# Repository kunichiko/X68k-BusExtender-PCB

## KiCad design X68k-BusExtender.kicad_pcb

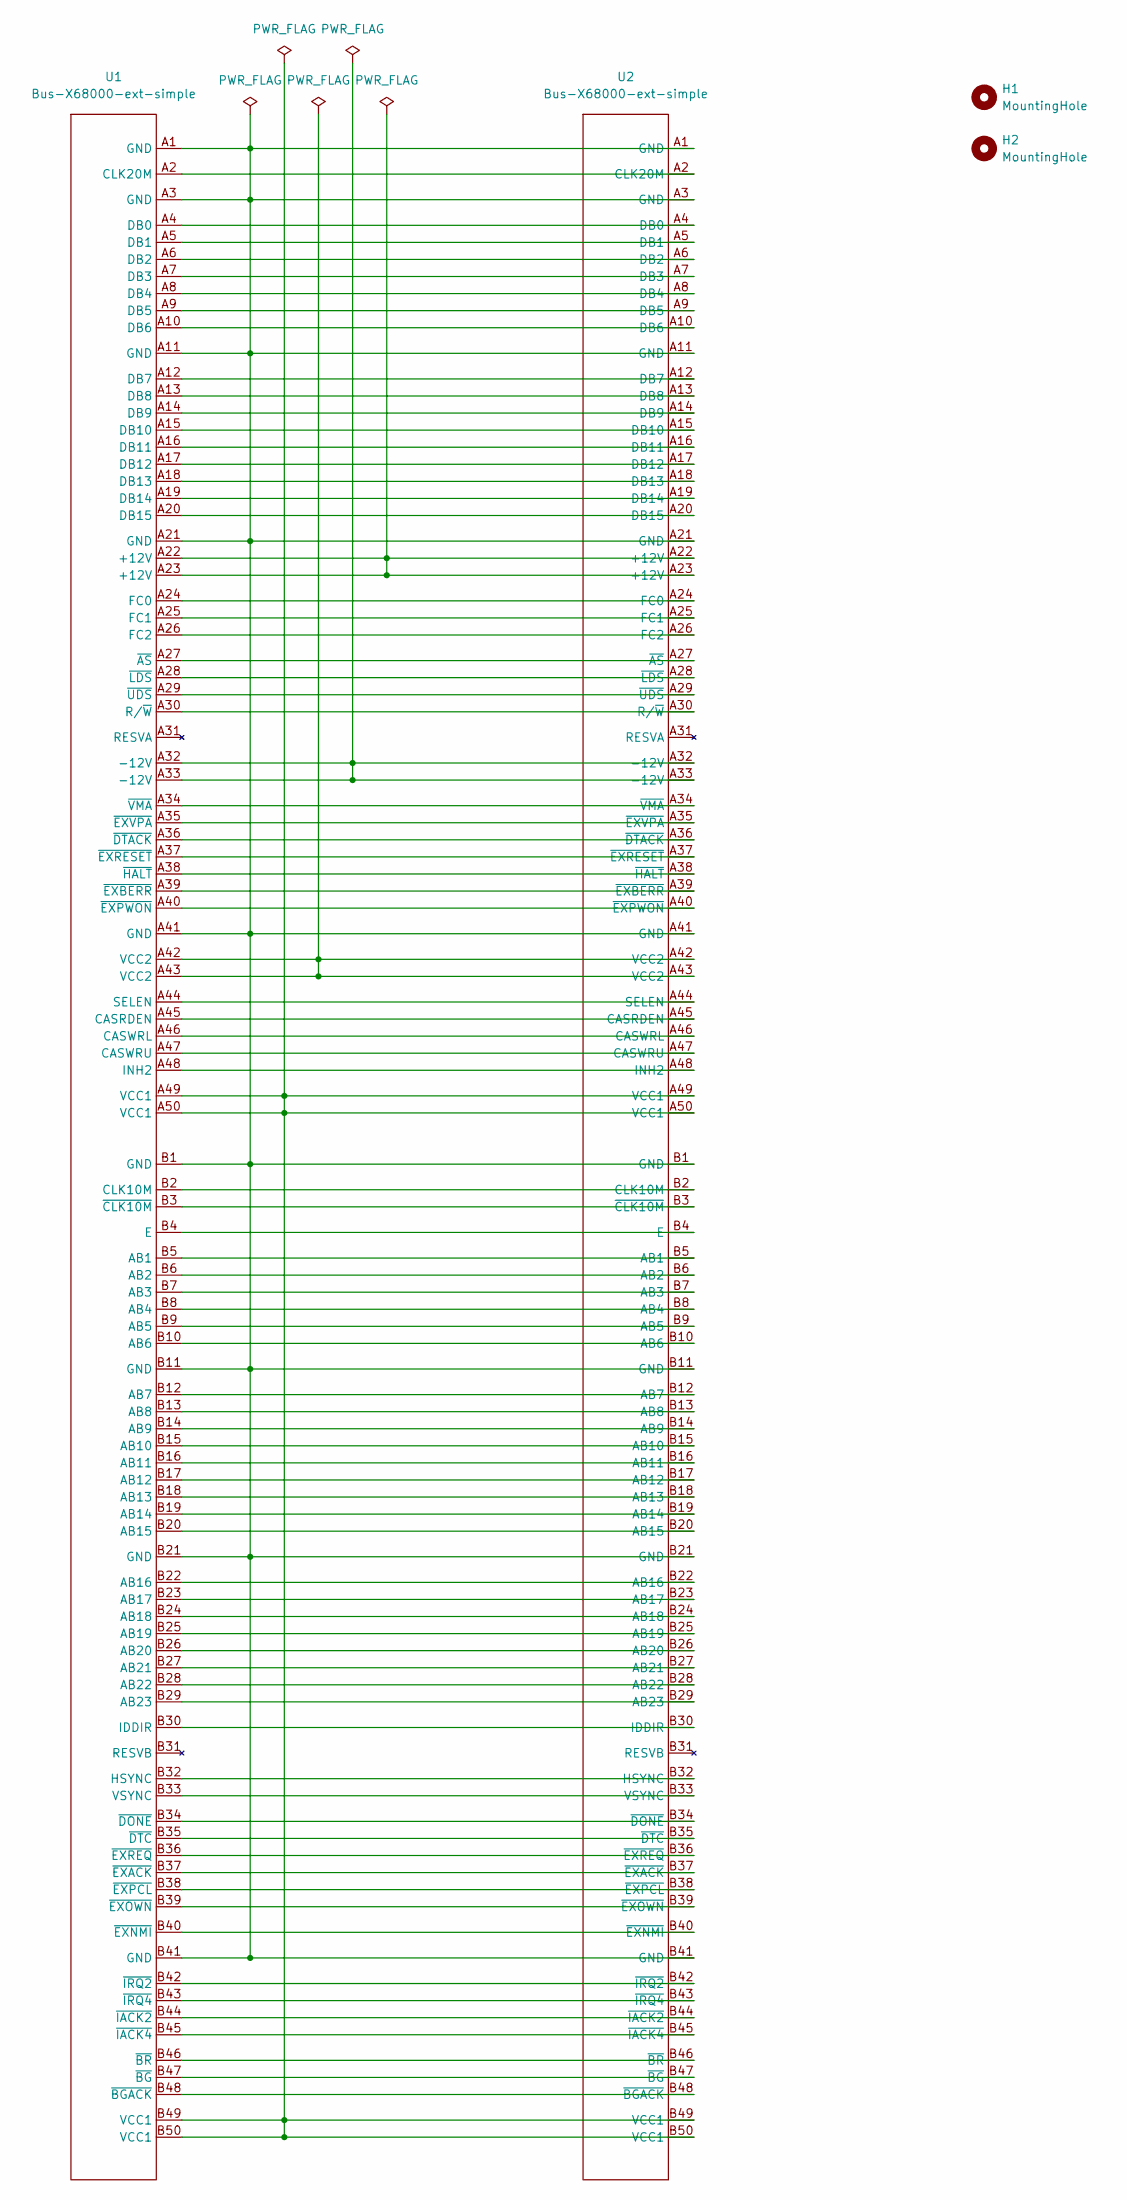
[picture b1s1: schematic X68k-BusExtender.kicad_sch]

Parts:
H1, H2: MountingHole; MountingHole_3.2mm_M3
U1: Bus-X68000-ext-simple; x68000-ext-cardedge-long
U2: Bus-X68000-ext-simple; Hirose-CR22-100D-2.54DS(70)

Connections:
unnamed: U1.A1 (GND), U1.A3 (GND), U1.A11 (GND), U1.A21 (GND), U1.A41 (GND), U1.B1 (GND), U1.B11 (GND), U1.B21 (GND), U1.B41 (GND), U2.A1 (GND), U2.A3 (GND), U2.A11 (GND), U2.A21 (GND), U2.A41 (GND), U2.B1 (GND), U2.B11 (GND), U2.B21 (GND), U2.B41 (GND)
unnamed: U1.A2 (CLK20M), U2.A2 (CLK20M)
unnamed: U1.A4 (DB0), U2.A4 (DB0)
unnamed: U1.A5 (DB1), U2.A5 (DB1)
unnamed: U1.A6 (DB2), U2.A6 (DB2)
unnamed: U1.A7 (DB3), U2.A7 (DB3)
unnamed: U1.A8 (DB4), U2.A8 (DB4)
unnamed: U1.A9 (DB5), U2.A9 (DB5)
unnamed: U1.A10 (DB6), U2.A10 (DB6)
unnamed: U1.A12 (DB7), U2.A12 (DB7)
unnamed: U1.A13 (DB8), U2.A13 (DB8)
unnamed: U1.A14 (DB9), U2.A14 (DB9)
unnamed: U1.A15 (DB10), U2.A15 (DB10)
unnamed: U1.A16 (DB11), U2.A16 (DB11)
unnamed: U1.A17 (DB12), U2.A17 (DB12)
unnamed: U1.A18 (DB13), U2.A18 (DB13)
unnamed: U1.A19 (DB14), U2.A19 (DB14)
unnamed: U1.A20 (DB15), U2.A20 (DB15)
unnamed: U1.A22 (+12V), U1.A23 (+12V), U2.A22 (+12V), U2.A23 (+12V)
unnamed: U1.A24 (FC0), U2.A24 (FC0)
unnamed: U1.A25 (FC1), U2.A25 (FC1)
unnamed: U1.A26 (FC2), U2.A26 (FC2)
unnamed: U1.A27 (~AS), U2.A27 (~AS)
unnamed: U1.A28 (~LDS), U2.A28 (~LDS)
unnamed: U1.A29 (~UDS), U2.A29 (~UDS)
unnamed: U1.A30 (R/~W), U2.A30 (R/~W)
unnamed: U1.A32 (-12V), U1.A33 (-12V), U2.A32 (-12V), U2.A33 (-12V)
unnamed: U1.A34 (~VMA), U2.A34 (~VMA)
unnamed: U1.A35 (~EXVPA), U2.A35 (~EXVPA)
unnamed: U1.A36 (~DTACK), U2.A36 (~DTACK)
unnamed: U1.A37 (~EXRESET), U2.A37 (~EXRESET)
unnamed: U1.A38 (~HALT), U2.A38 (~HALT)
unnamed: U1.A39 (~EXBERR), U2.A39 (~EXBERR)
unnamed: U1.A40 (~EXPWON), U2.A40 (~EXPWON)
unnamed: U1.A42 (VCC2), U1.A43 (VCC2), U2.A42 (VCC2), U2.A43 (VCC2)
unnamed: U1.A44 (SELEN), U2.A44 (SELEN)
unnamed: U1.A45 (CASRDEN), U2.A45 (CASRDEN)
unnamed: U1.A46 (CASWRL), U2.A46 (CASWRL)
unnamed: U1.A47 (CASWRU), U2.A47 (CASWRU)
unnamed: U1.A48 (INH2), U2.A48 (INH2)
unnamed: U1.A49 (VCC1), U1.A50 (VCC1), U1.B49 (VCC1), U1.B50 (VCC1), U2.A49 (VCC1), U2.A50 (VCC1), U2.B49 (VCC1), U2.B50 (VCC1)
unnamed: U1.B2 (CLK10M), U2.B2 (CLK10M)
unnamed: U1.B3 (~CLK10M), U2.B3 (~CLK10M)
unnamed: U1.B4 (E), U2.B4 (E)
unnamed: U1.B5 (AB1), U2.B5 (AB1)
unnamed: U1.B6 (AB2), U2.B6 (AB2)
unnamed: U1.B7 (AB3), U2.B7 (AB3)
unnamed: U1.B8 (AB4), U2.B8 (AB4)
unnamed: U1.B9 (AB5), U2.B9 (AB5)
unnamed: U1.B10 (AB6), U2.B10 (AB6)
unnamed: U1.B12 (AB7), U2.B12 (AB7)
unnamed: U1.B13 (AB8), U2.B13 (AB8)
unnamed: U1.B14 (AB9), U2.B14 (AB9)
unnamed: U1.B15 (AB10), U2.B15 (AB10)
unnamed: U1.B16 (AB11), U2.B16 (AB11)
unnamed: U1.B17 (AB12), U2.B17 (AB12)
unnamed: U1.B18 (AB13), U2.B18 (AB13)
unnamed: U1.B19 (AB14), U2.B19 (AB14)
unnamed: U1.B20 (AB15), U2.B20 (AB15)
unnamed: U1.B22 (AB16), U2.B22 (AB16)
unnamed: U1.B23 (AB17), U2.B23 (AB17)
unnamed: U1.B24 (AB18), U2.B24 (AB18)
unnamed: U1.B25 (AB19), U2.B25 (AB19)
unnamed: U1.B26 (AB20), U2.B26 (AB20)
unnamed: U1.B27 (AB21), U2.B27 (AB21)
unnamed: U1.B28 (AB22), U2.B28 (AB22)
unnamed: U1.B29 (AB23), U2.B29 (AB23)
unnamed: U1.B30 (IDDIR), U2.B30 (IDDIR)
unnamed: U1.B32 (HSYNC), U2.B32 (HSYNC)
unnamed: U1.B33 (VSYNC), U2.B33 (VSYNC)
unnamed: U1.B34 (~DONE), U2.B34 (~DONE)
unnamed: U1.B35 (~DTC), U2.B35 (~DTC)
unnamed: U1.B36 (~EXREQ), U2.B36 (~EXREQ)
unnamed: U1.B37 (~EXACK), U2.B37 (~EXACK)
unnamed: U1.B38 (~EXPCL), U2.B38 (~EXPCL)
unnamed: U1.B39 (~EXOWN), U2.B39 (~EXOWN)
unnamed: U1.B40 (~EXNMI), U2.B40 (~EXNMI)
unnamed: U1.B42 (~IRQ2), U2.B42 (~IRQ2)
unnamed: U1.B43 (~IRQ4), U2.B43 (~IRQ4)
unnamed: U1.B44 (~IACK2), U2.B44 (~IACK2)
unnamed: U1.B45 (~IACK4), U2.B45 (~IACK4)
unnamed: U1.B46 (~BR), U2.B46 (~BR)
unnamed: U1.B47 (~BG), U2.B47 (~BG)
unnamed: U1.B48 (~BGACK), U2.B48 (~BGACK)

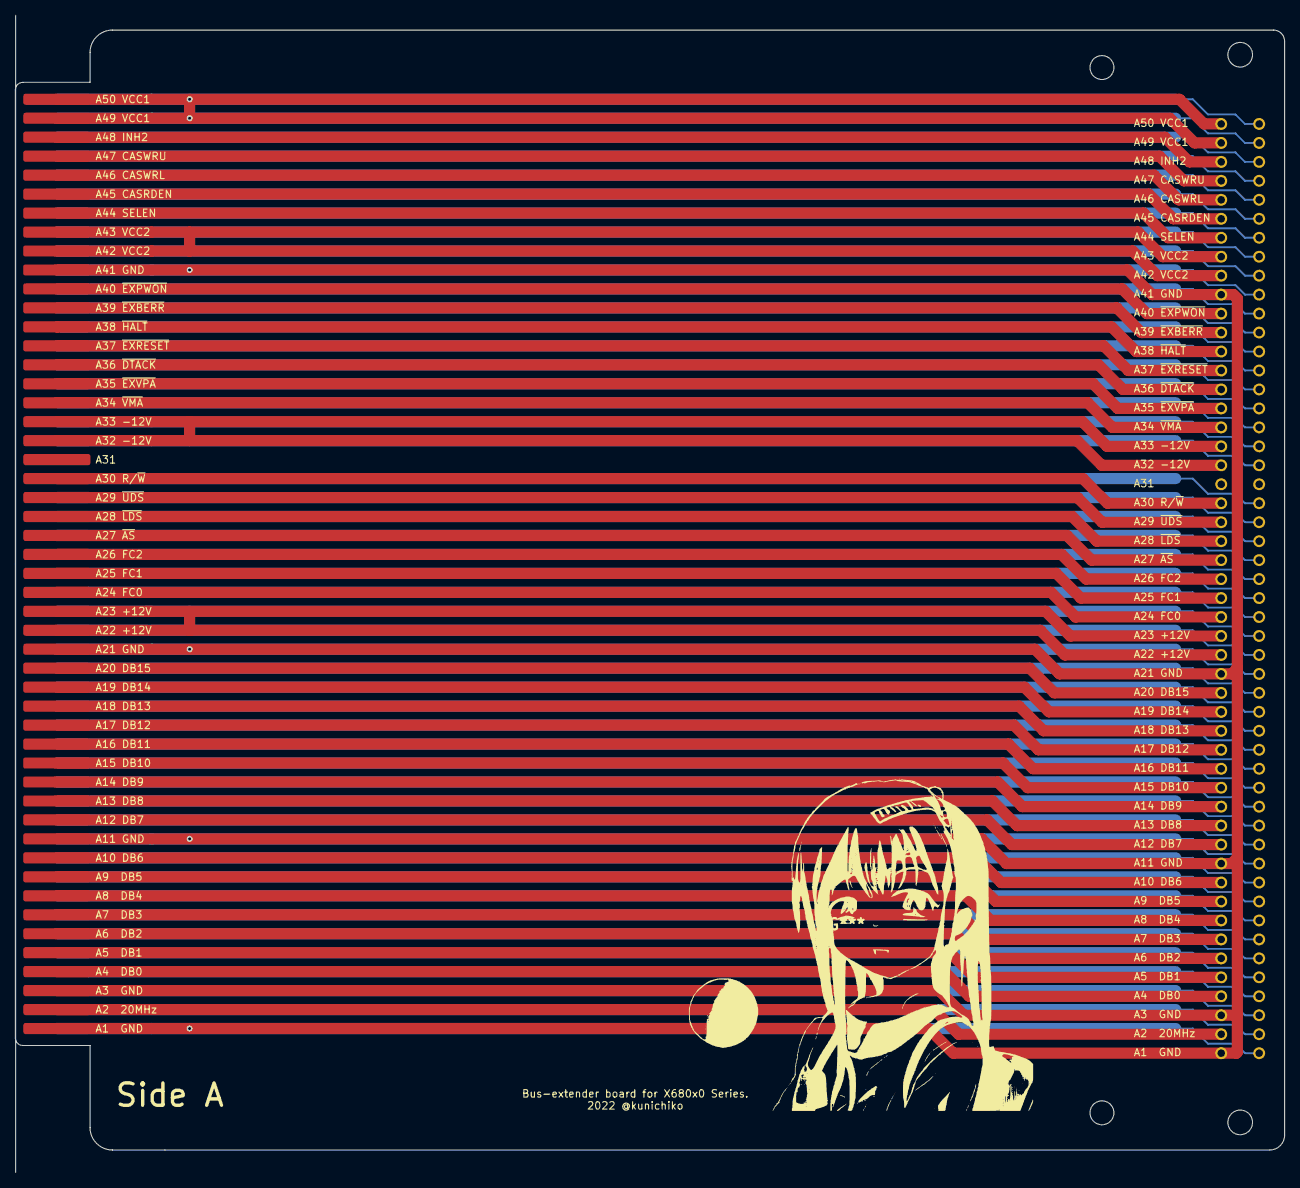
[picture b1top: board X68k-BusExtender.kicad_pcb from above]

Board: 2 copper layers, 170.0 x 155.0 mm, 4 parts (0 on the bottom side), 84 nets.

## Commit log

2022-09-08 Initial commit.
2022-09-11 Ver 1
2022-09-11 V1.0
2022-09-12 Add git ignore
